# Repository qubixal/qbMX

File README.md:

# qbMX

> A custom mechanical keyboard built from scratch for [Hack Club Keeb](https://keeb.hackclub.com/) YSWS.

## Overview

**qbMX** is a fully custom mechanical keyboard designed in KiCad and Fusion. It features:

- **85-key (79+6) layout** with a rotary encoder, modelled after Apple's Magic Keyboard.
- **Cherry MX Low-Profile Red** switches, and on-plate stabalisers (instead of on-pcb)
- Uses the **RP2040 microcontroller** (Orpheus Pico)
- A 0.91" **128x32 OLED display**
- 15 mini-LEDs at the top of the keyboard
- Custom PCB, ordered and assembled by me

## Why I Built qbMX

I wanted to learn about and build a keyboard myself, since I'd never done it before.
Designing the matrix and optimising GPIO lanes with functionality was a cool challenge. Oh, and I just wanted a keyboard; and Keeb gave me an excuse to make it.

## What's in This Repo

| Path | Description |
| --- | --- |
| `keeb.kicad_sch` | Schematic |
| `keeb.kicad_pcb` / `keeb.kicad_pro` | KiCad PCB layout & project |
| `pcb/` + `pcb.zip` | Gerbers & drill files (F.Cu, B.Cu, silkscreen, mask, Edge.Cuts) |
| `*.step` | 3D models (board, OLED, rotary encoder, plate) |
| `key-switches.pretty/`, `extra_key.pretty/` | Footprint libraries |
| `readme-library/` | Photos & renders |
| `bom.csv` | Bill of materials |

## Use Guide

After building all physical hardware, download the firmware folder then:

```cmd
export PICO_SDK_PATH=/path/to/pico-sdk

cd firmware && mkdir build && cd build

cmake .. && make
```

hold BOOTSEL on the Pico, plug in the USB and drag qbmx.uf2 to the mass storage device.

OLED Shows 5 pages:
0. Current keyboard layer
1. Custom text/bitmap
2. LED mode + brightness
3. WPM counter with bar graph
4. Host temps (CPU avg, GPU avg, Pico internal temp)

For temperature tracking to work properly,
1. Install pyserial
```cmd
pip3 install pyserial
```
2. Run host script which auto-detects the Pico port
```cmd
python3 firmware/host_temp.py
```

> **Note:** osx-cpu-temp will return 0.0°C on Apple Silicon Macs without SMC entitlements; where the OLED will show N/A in this case. You may instead compile `osx-cpu-temp` from source or use  `sudo powermetrics`.

### Programmable Keys (Column 14, Rows 0-5)
By default they are mapped to F13-F18 (USB HID keycodes 0x68 -> 0x6D), which is recognised by every major OS. It can be remapped in system settings.

Other functions include:
Short press rotary encoder to pause, Long press rotary encoder to toggle between volume and brightness (backlight) mode

## Build Log / Journal

See [`JOURNAL.md`](JOURNAL.md).

## BOM

See [`bom.csv`](bom.csv).

## Acknowledgements

- [Hack Club Keeb](https://keeb.hackclub.com/) for the program
- siderakb/key-switches.pretty and eblaster/marbastlib libraries
- GrabCAD models [switch](https://grabcad.com/library/low-profile-cherry-mx-red-1), [encoder](https://grabcad.com/library/11mm-metal-shaft-rotary-encoders-tht-vertical-w-push-on-switch-1), [OLED](https://grabcad.com/library/0-91-128x32-oled-display-1)
- Github models [keycaps](https://github.com/anhthang/dsa-keycap/)

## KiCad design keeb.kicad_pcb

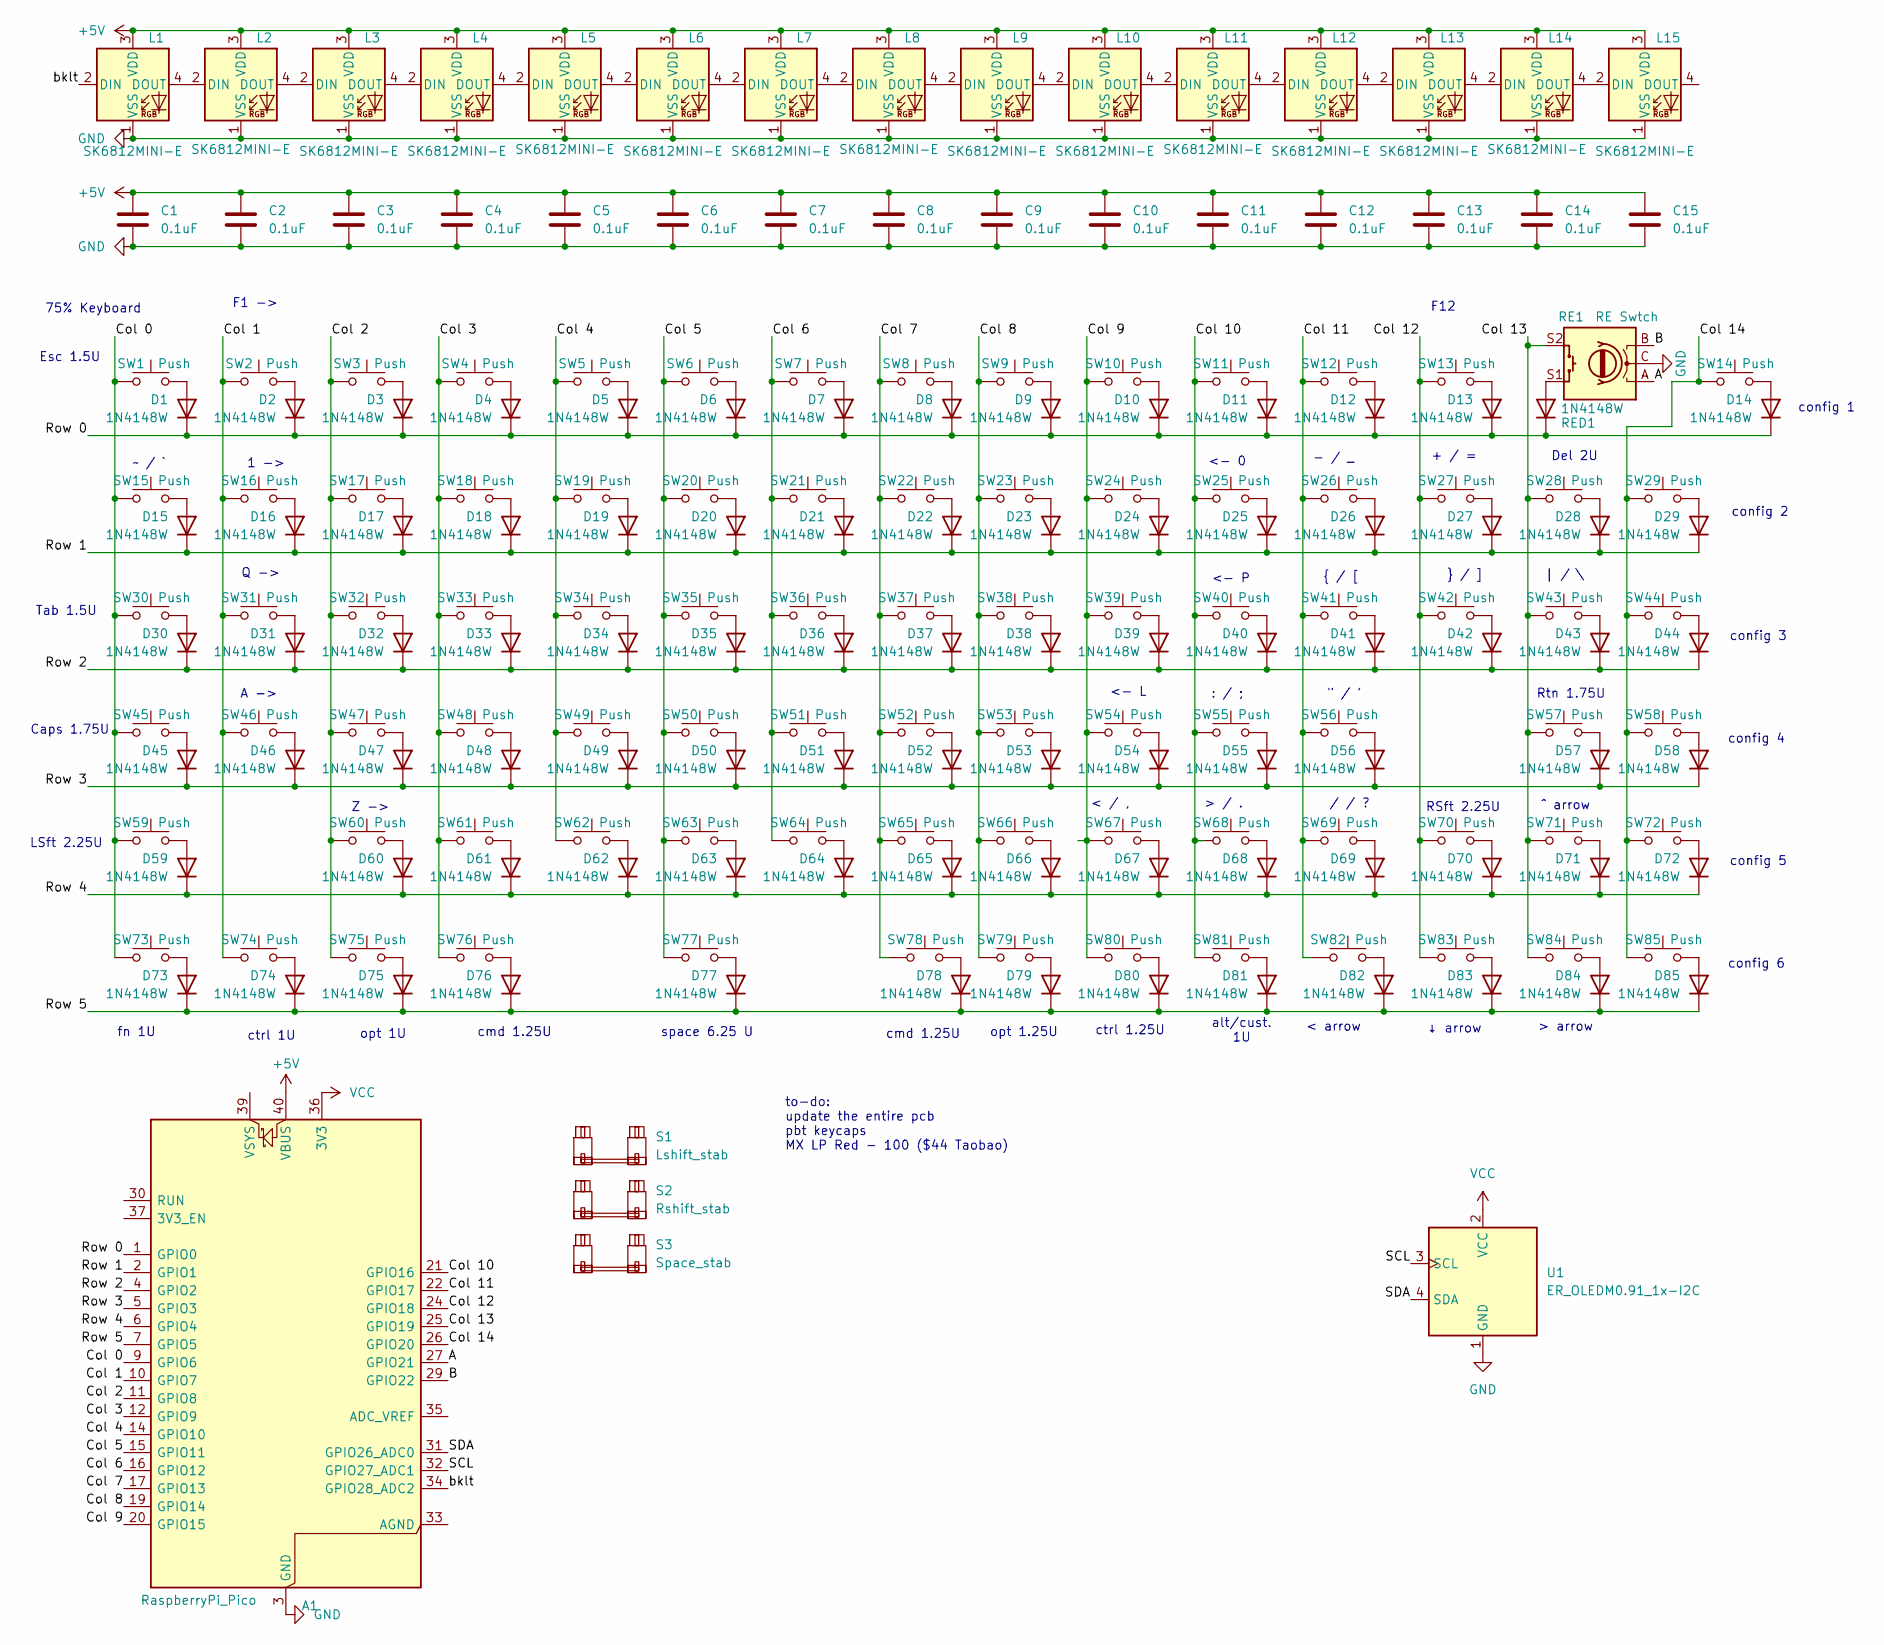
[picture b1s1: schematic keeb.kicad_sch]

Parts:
A1: RaspberryPi_Pico; RaspberryPi_Pico_Common_THT
C1, C2, C3, C4, C5, C6, C7, C8, C9, C10, C11, C12, C13, C14, C15: 0.1uF; C_0603_1608Metric
D1, D2, D3, D4, D5, D6, D7, D8, D9, D10, D11, D12, D13, D14, D15, D16, D17, D18, D19, D20, D21, D22, D23, D24, D25, D26, D27, D28, D29, D30, D31, D32, D33, D34, D35, D36, D37, D38, D39, D40, D41, D42, D43, D44, D45, D46, D47, D48, D49, D50, D51, D52, D53, D54, D55, D56, D57, D58, D59, D60, D61, D62, D63, D64, D65, D66, D67, D68, D69, D70, D71, D72, D73, D74, D75, D76, D77, D78, D79, D80, D81, D82, D83, D84, D85: 1N4148W; D_SOD-123
L1, L2, L3, L4, L5, L6, L7, L8, L9, L10, L11, L12, L13, L14, L15: SK6812MINI-E; LED_SK6812MINI-E_3.2x2.8mm_P1.5mm_ReverseMount
RE1: RE Swtch; RotaryEncoder_Alps_EC11E-Switch_Vertical_H20mm_CircularMoun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
RED1: 1N4148W; D_SOD-123
S1: Lshift_stab; STAB_MX_P_2u
S2: Rshift_stab; STAB_MX_P_2u
S3: Space_stab; STAB_MX_6.25u
SW1, SW2, SW3, SW4, SW5, SW6, SW7, SW8, SW9, SW10, SW11, SW12, SW13, SW14, SW15, SW16, SW17, SW18, SW19, SW20, SW21, SW22, SW23, SW24, SW25, SW26, SW27, SW28, SW29, SW30, SW31, SW32, SW33, SW34, SW35, SW36, SW37, SW38, SW39, SW40, SW41, SW42, SW43, SW44, SW45, SW46, SW47, SW48, SW49, SW50, SW51, SW52, SW53, SW54, SW55, SW56, SW57, SW58, SW59, SW60, SW61, SW62, SW63, SW64, SW65, SW66, SW67, SW68, SW69, SW70, SW71, SW72, SW73, SW74, SW75, SW76, SW77, SW78, SW79, SW80, SW81, SW82, SW83, SW84, SW85: Push; SW_MX_LowProfile_THT
U1: ER_OLEDM0.91_1x-I2C

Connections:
+5V: A1.40 (VBUS), C1.1, C2.1, C3.1, C4.1, C5.1, C6.1, C7.1, C8.1, C9.1, C10.1, C11.1, C12.1, C13.1, C14.1, C15.1, L1.3 (VDD), L2.3 (VDD), L3.3 (VDD), L4.3 (VDD), L5.3 (VDD), L6.3 (VDD), L7.3 (VDD), L8.3 (VDD), L9.3 (VDD), L10.3 (VDD), L11.3 (VDD), L12.3 (VDD), L13.3 (VDD), L14.3 (VDD), L15.3 (VDD)
/A: A1.27 (GPIO21), RE1.A
/B: A1.29 (GPIO22), RE1.B
/Col 0: A1.9 (GPIO6), SW1.1, SW15.1, SW30.1, SW45.1, SW59.1, SW73.1
/Col 1: A1.10 (GPIO7), SW2.1, SW16.1, SW31.1, SW46.1, SW74.1
/Col 2: A1.11 (GPIO8), SW3.1, SW17.1, SW32.1, SW47.1, SW60.1, SW75.1
/Col 3: A1.12 (GPIO9), SW4.1, SW18.1, SW33.1, SW48.1, SW61.1, SW76.1
/Col 4: A1.14 (GPIO10), SW5.1, SW19.1, SW34.1, SW49.1, SW62.1
/Col 5: A1.15 (GPIO11), SW6.1, SW20.1, SW35.1, SW50.1, SW63.1, SW77.1
/Col 6: A1.16 (GPIO12), SW7.1, SW21.1, SW36.1, SW51.1, SW64.1
/Col 7: A1.17 (GPIO13), SW8.1, SW22.1, SW37.1, SW52.1, SW65.1, SW78.1
/Col 8: A1.19 (GPIO14), SW9.1, SW23.1, SW38.1, SW53.1, SW66.1, SW79.1
/Col 9: A1.20 (GPIO15), SW10.1, SW24.1, SW39.1, SW54.1, SW67.1, SW80.1
/Col 10: A1.21 (GPIO16), SW11.1, SW25.1, SW40.1, SW55.1, SW68.1, SW81.1
/Col 11: A1.22 (GPIO17), SW12.1, SW26.1, SW41.1, SW56.1, SW69.1, SW82.1
/Col 12: A1.24 (GPIO18), SW13.1, SW27.1, SW42.1, SW70.1, SW83.1
/Col 13: A1.25 (GPIO19), RE1.S2, SW28.1, SW43.1, SW57.1, SW71.1, SW84.1
/Col 14: A1.26 (GPIO20), SW14.1, SW29.1, SW44.1, SW58.1, SW72.1, SW85.1
/Row 0: A1.1 (GPIO0), D1.1 (K), D2.1 (K), D3.1 (K), D4.1 (K), D5.1 (K), D6.1 (K), D7.1 (K), D8.1 (K), D9.1 (K), D10.1 (K), D11.1 (K), D12.1 (K), D13.1 (K), D14.1 (K), RED1.1 (K)
/Row 1: A1.2 (GPIO1), D15.1 (K), D16.1 (K), D17.1 (K), D18.1 (K), D19.1 (K), D20.1 (K), D21.1 (K), D22.1 (K), D23.1 (K), D24.1 (K), D25.1 (K), D26.1 (K), D27.1 (K), D28.1 (K), D29.1 (K)
/Row 2: A1.4 (GPIO2), D30.1 (K), D31.1 (K), D32.1 (K), D33.1 (K), D34.1 (K), D35.1 (K), D36.1 (K), D37.1 (K), D38.1 (K), D39.1 (K), D40.1 (K), D41.1 (K), D42.1 (K), D43.1 (K), D44.1 (K)
/Row 3: A1.5 (GPIO3), D45.1 (K), D46.1 (K), D47.1 (K), D48.1 (K), D49.1 (K), D50.1 (K), D51.1 (K), D52.1 (K), D53.1 (K), D54.1 (K), D55.1 (K), D56.1 (K), D57.1 (K), D58.1 (K)
/Row 4: A1.6 (GPIO4), D59.1 (K), D60.1 (K), D61.1 (K), D62.1 (K), D63.1 (K), D64.1 (K), D65.1 (K), D66.1 (K), D67.1 (K), D68.1 (K), D69.1 (K), D70.1 (K), D71.1 (K), D72.1 (K)
/Row 5: A1.7 (GPIO5), D73.1 (K), D74.1 (K), D75.1 (K), D76.1 (K), D77.1 (K), D78.1 (K), D79.1 (K), D80.1 (K), D81.1 (K), D82.1 (K), D83.1 (K), D84.1 (K), D85.1 (K)
/SCL: A1.32 (GPIO27_ADC1), U1.3 (SCL)
/SDA: A1.31 (GPIO26_ADC0), U1.4 (SDA)
/bklt: A1.34 (GPIO28_ADC2), L1.2 (DIN)
GND: A1.3 (GND), A1.8 (GND), A1.13 (GND), A1.18 (GND), A1.23 (GND), A1.28 (GND), A1.38 (GND), C1.2, C2.2, C3.2, C4.2, C5.2, C6.2, C7.2, C8.2, C9.2, C10.2, C11.2, C12.2, C13.2, C14.2, C15.2, L1.1 (VSS), L2.1 (VSS), L3.1 (VSS), L4.1 (VSS), L5.1 (VSS), L6.1 (VSS), L7.1 (VSS), L8.1 (VSS), L9.1 (VSS), L10.1 (VSS), L11.1 (VSS), L12.1 (VSS), L13.1 (VSS), L14.1 (VSS), L15.1 (VSS), RE1.C, U1.1 (GND)
unnamed: D1.2 (A), SW1.2
unnamed: D2.2 (A), SW2.2
unnamed: D3.2 (A), SW3.2
unnamed: D4.2 (A), SW4.2
unnamed: D5.2 (A), SW5.2
unnamed: D6.2 (A), SW6.2
unnamed: D7.2 (A), SW7.2
unnamed: D8.2 (A), SW8.2
unnamed: D9.2 (A), SW9.2
unnamed: D10.2 (A), SW10.2
unnamed: D11.2 (A), SW11.2
unnamed: D12.2 (A), SW12.2
unnamed: D13.2 (A), SW13.2
unnamed: D14.2 (A), SW14.2
unnamed: D15.2 (A), SW15.2
unnamed: D16.2 (A), SW16.2
unnamed: D17.2 (A), SW17.2
unnamed: D18.2 (A), SW18.2
unnamed: D19.2 (A), SW19.2
unnamed: D20.2 (A), SW20.2
unnamed: D21.2 (A), SW21.2
unnamed: D22.2 (A), SW22.2
unnamed: D23.2 (A), SW23.2
unnamed: D24.2 (A), SW24.2
unnamed: D25.2 (A), SW25.2
unnamed: D26.2 (A), SW26.2
unnamed: D27.2 (A), SW27.2
unnamed: D28.2 (A), SW28.2
unnamed: D29.2 (A), SW29.2
unnamed: D30.2 (A), SW30.2
unnamed: D31.2 (A), SW31.2
unnamed: D32.2 (A), SW32.2
unnamed: D33.2 (A), SW33.2
unnamed: D34.2 (A), SW34.2
unnamed: D35.2 (A), SW35.2
unnamed: D36.2 (A), SW36.2
unnamed: D37.2 (A), SW37.2
unnamed: D38.2 (A), SW38.2
unnamed: D39.2 (A), SW39.2
unnamed: D40.2 (A), SW40.2
unnamed: D41.2 (A), SW41.2
unnamed: D42.2 (A), SW42.2
unnamed: D43.2 (A), SW43.2
unnamed: D44.2 (A), SW44.2
unnamed: D45.2 (A), SW45.2
unnamed: D46.2 (A), SW46.2
unnamed: D47.2 (A), SW47.2
unnamed: D48.2 (A), SW48.2
unnamed: D49.2 (A), SW49.2
unnamed: D50.2 (A), SW50.2
unnamed: D51.2 (A), SW51.2
unnamed: D52.2 (A), SW52.2
unnamed: D53.2 (A), SW53.2
unnamed: D54.2 (A), SW54.2
unnamed: D55.2 (A), SW55.2
unnamed: D56.2 (A), SW56.2
unnamed: D57.2 (A), SW57.2
unnamed: D58.2 (A), SW58.2
unnamed: D59.2 (A), SW59.2
unnamed: D60.2 (A), SW60.2
unnamed: D61.2 (A), SW61.2
unnamed: D62.2 (A), SW62.2
unnamed: D63.2 (A), SW63.2
unnamed: D64.2 (A), SW64.2
unnamed: D65.2 (A), SW65.2
unnamed: D66.2 (A), SW66.2
unnamed: D67.2 (A), SW67.2
unnamed: D68.2 (A), SW68.2
unnamed: D69.2 (A), SW69.2
unnamed: D70.2 (A), SW70.2
unnamed: D71.2 (A), SW71.2
unnamed: D72.2 (A), SW72.2
unnamed: D73.2 (A), SW73.2
unnamed: D74.2 (A), SW74.2
unnamed: D75.2 (A), SW75.2
unnamed: D76.2 (A), SW76.2
unnamed: D77.2 (A), SW77.2
unnamed: D78.2 (A), SW78.2
unnamed: D79.2 (A), SW79.2
unnamed: D80.2 (A), SW80.2
unnamed: D81.2 (A), SW81.2
unnamed: D82.2 (A), SW82.2
unnamed: D83.2 (A), SW83.2
unnamed: D84.2 (A), SW84.2
unnamed: D85.2 (A), SW85.2
unnamed: L1.4 (DOUT), L2.2 (DIN)
unnamed: L2.4 (DOUT), L3.2 (DIN)
unnamed: L3.4 (DOUT), L4.2 (DIN)
unnamed: L4.4 (DOUT), L5.2 (DIN)
unnamed: L5.4 (DOUT), L6.2 (DIN)
unnamed: L6.4 (DOUT), L7.2 (DIN)
unnamed: L7.4 (DOUT), L8.2 (DIN)
unnamed: L8.4 (DOUT), L9.2 (DIN)
unnamed: L9.4 (DOUT), L10.2 (DIN)
unnamed: L10.4 (DOUT), L11.2 (DIN)
unnamed: L11.4 (DOUT), L12.2 (DIN)
unnamed: L12.4 (DOUT), L13.2 (DIN)
unnamed: L13.4 (DOUT), L14.2 (DIN)
unnamed: L14.4 (DOUT), L15.2 (DIN)
unnamed: RE1.S1, RED1.2 (A)
VCC: A1.36 (3V3), U1.2 (VCC)

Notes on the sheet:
config 1
F12
: / ;
config 5
> / .
Caps 1.75U
opt 1.25U
F1 ->
} / ]
config 6
Q ->
75% Keyboard
< / ,
fn 1U
cmd 1.25U
Tab 1.5U
↓ arrow
| / \
- / _
^ arrow
> arrow
Del 2U
LSft 2.25U
space 6.25 U
ctrl 1.25U
Rtn 1.75U
config 2
~ / `
<- 0
{ / [
config 4
1 ->
<- P
<- L
config 3
opt 1U
" / '
Esc 1.5U
A ->
to-do: update the entire pcb pbt keycaps MX LP Red - 100 ($44 Taobao)

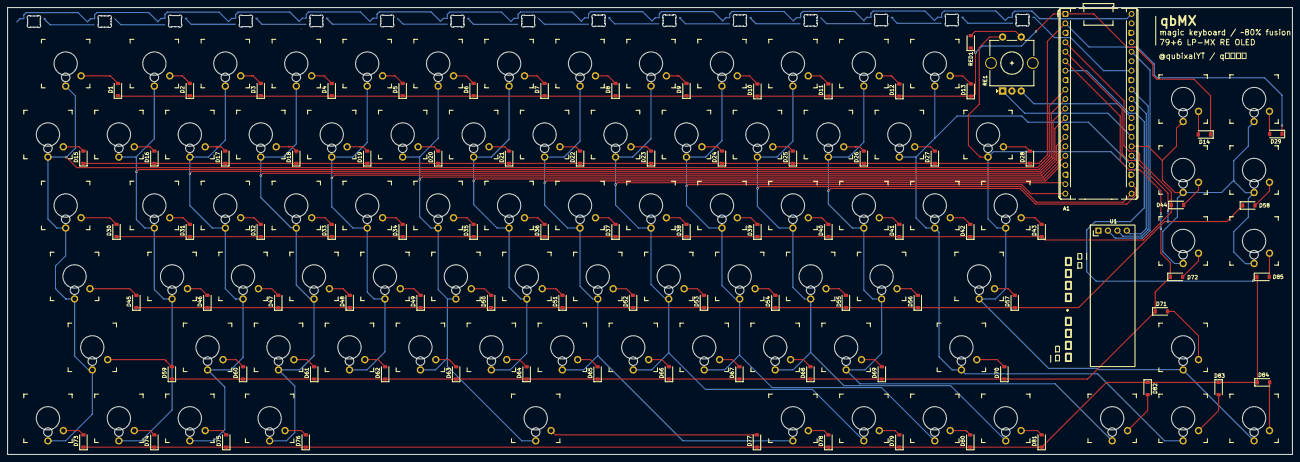
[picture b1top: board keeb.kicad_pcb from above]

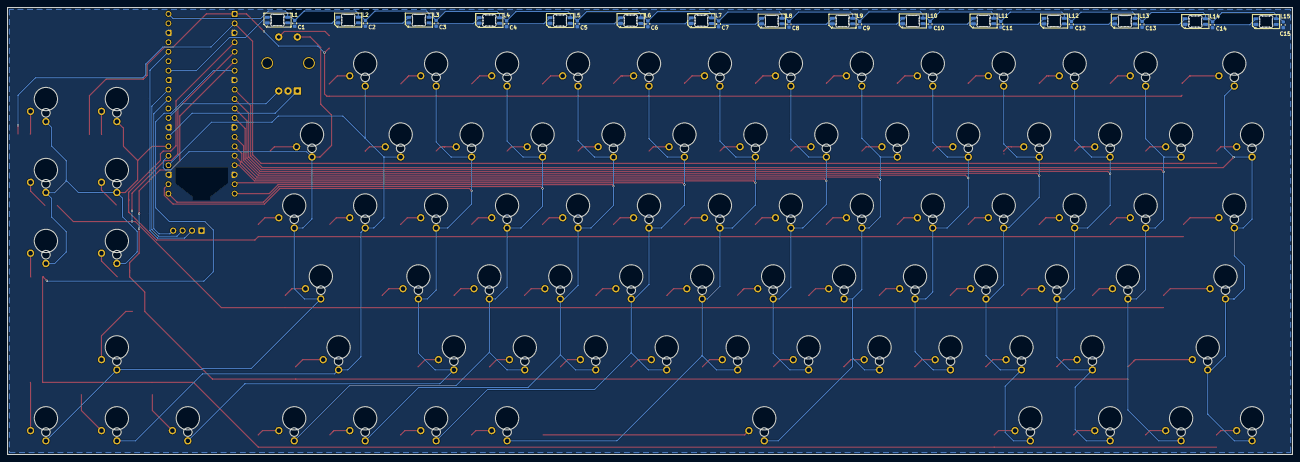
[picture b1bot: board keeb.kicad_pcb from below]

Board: 2 copper layers, 345.0 x 120.0 mm, 204 parts (30 on the bottom side), 129 nets.

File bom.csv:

Designator,Item,Item No/LCSC,Supplier,Variant,Qty,Unit $AUD,Total $AUD,Link
1,Orpheus Pico,,Hack Club,,1,?,?,
2,Cherry MX Low Profile Red,CHERRY__________________MX Low Profile RGB,Taobao,100 pack,1,46.04,46.04,https://item.taobao.com/item.htm?id=673935710462
3,Plate Mount Stab,__Chosfox MX________ ______________ ,Taobao,6.25u*1+2u*2,1,5.6,5.6,https://item.taobao.com/item.htm?id=921829717536
4,M3*10 Screw,M2.5M3M4M5M6M8__304___________________,Taobao,50 pack,1,1.45,1.45,https://detail.tmall.com/item.htm?id=650868762254
5,M2*3 Screw,M2_______CM__3.3_0.3_______*2/2.5/3/4/5/10,Taobao,100 pack,1,0.62,0.62,https://detail.tmall.com/item.htm?id=610559538489
6,EC11 Rotary Encoder,EC11________10/15/20/25mm__ ___________,Taobao,__10mm,1,1.54,1.54,https://item.taobao.com/item.htm?id=586360534043
7,1N4148W Diode,C84367,LCSC,,100,0.01,1,https://www.lcsc.com/product-detail/C84367.html
8,"0.91"" OLED Screen",0.91_OLED_____128_32___4_iic__SSD1306,Taobao,4PIN 0.91_ _______,1,1.8,1.8,https://item.taobao.com/item.htm?id=824313570601
9,0.1uF 0603 Cap,C14663,LCSC,,50,0.02,1,https://www.lcsc.com/product-detail/C14663.html
10,OPSCO Optoelectronics SK6812MINI-E,C5149201,LCSC,,15,0.11,1.65,https://www.lcsc.com/product-detail/C5149201.html
11,PCB - Keyboard,,?,,1,32.99,32.99,
12,PCB - Plate (FR4),,?,1.2mm,1,34.95,34.95,
13,Case (3D print + Acrylic),-,-,-,-,-,-,
14,Silicone Padding,______________________________,Taobao,15 pack 30*9*1mm,1,1.03,1.03,
15,PBT Keycaps,______ABS\PBT____68\84\98\104\87\100\108__,Taobao,PBT White Set,1,10.87,10.87,
,,,,,,TOTAL,140.54,
,,,,,,TOTAL (USD),101.1888,
